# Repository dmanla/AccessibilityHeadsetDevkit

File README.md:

# AccessibilityHeadsetDevkit
A development kit for the creation of an accessibility driven platform.

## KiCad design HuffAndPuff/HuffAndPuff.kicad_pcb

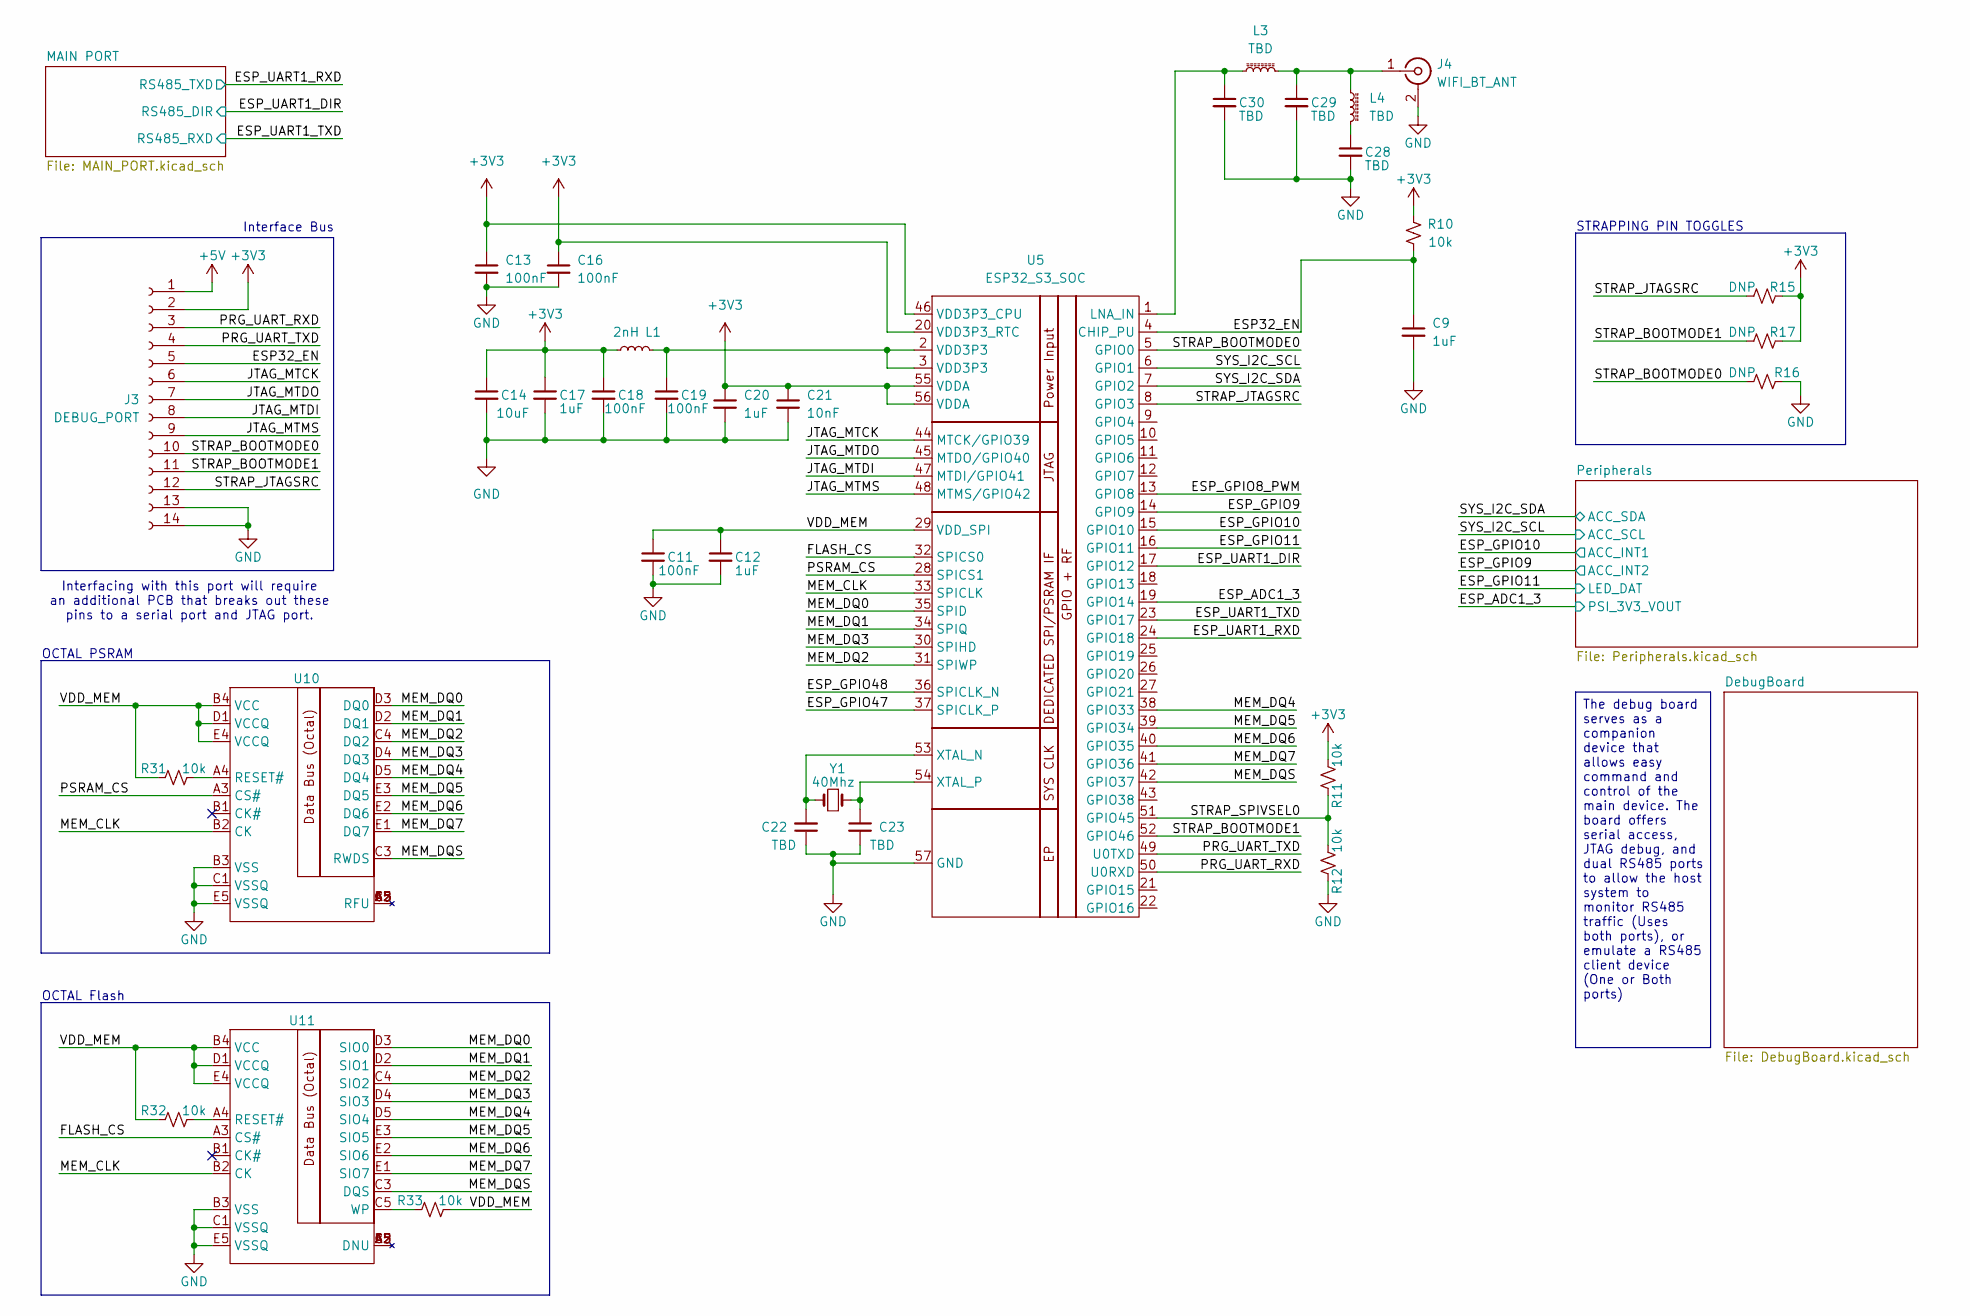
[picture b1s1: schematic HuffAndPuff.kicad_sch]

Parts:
C9, C12, C17, C20: 1uF; C_0402_1005Metric_Pad0.74x0.62mm_HandSolder
C11, C13, C16, C18, C19: 100nF; C_0402_1005Metric_Pad0.74x0.62mm_HandSolder
C14: 10uF; C_0603_1608Metric_Pad1.08x0.95mm_HandSolder
C21: 10nF; C_0402_1005Metric_Pad0.74x0.62mm_HandSolder
C22, C23, C28, C29, C30: TBD; C_0402_1005Metric_Pad0.74x0.62mm_HandSolder
J3: DEBUG_PORT; TE_1-1734839-4_1x14-1MP_P0.5mm_Horizontal
J4: WIFI_BT_ANT; SMA_Molex_73251-2200_Horizontal
L1: 2nH; L_0402_1005Metric_Pad0.77x0.64mm_HandSolder
L3, L4: TBD; L_0402_1005Metric_Pad0.77x0.64mm_HandSolder
R10, R11, R12, R31, R32, R33: 10k; R_0402_1005Metric_Pad0.72x0.64mm_HandSolder
R15, R16, R17: DNP; R_0805_2012Metric_Pad1.20x1.40mm_HandSolder
U5: ESP32_S3_SOC; QFN-56-1EP_7x7mm_P0.4mm_EP5.6x5.6mm
U10, U11: BGA-24_5x5_6.0x8.0mm
Y1: 40Mhz; Crystal_SMD_3215-2Pin_3.2x1.5mm

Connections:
+3V3: C13.1, C14.1, C16.1, C17.1, C18.1, C20.1, C21.1, J3.2, L1.1, R10.1, R11.1, R15.2, R17.2, U5.20 (VDD3P3_RTC), U5.46 (VDD3P3_CPU), U5.55 (VDDA), U5.56 (VDDA); also elsewhere on the board
+5V: J3.1; also elsewhere on the board
/ESP32_EN: C9.1, J3.5, R10.2, U5.4 (CHIP_PU)
/ESP_ADC1_3: U5.19 (GPIO14); also elsewhere on the board
/ESP_GPIO8_PWM: U5.13 (GPIO8)
/ESP_GPIO9: U5.14 (GPIO9); also elsewhere on the board
/ESP_GPIO10: U5.15 (GPIO10); also elsewhere on the board
/ESP_GPIO11: U5.16 (GPIO11); also elsewhere on the board
/ESP_GPIO47: U5.37 (SPICLK_P)
/ESP_GPIO48: U5.36 (SPICLK_N)
/ESP_UART1_DIR: U5.17 (GPIO12); also elsewhere on the board
/ESP_UART1_RXD: U5.24 (GPIO18); also elsewhere on the board
/ESP_UART1_TXD: U5.23 (GPIO17); also elsewhere on the board
/FLASH_CS: U5.32 (SPICS0), U11.A3 (CS#)
/JTAG_MTCK: J3.6, U5.44 (MTCK/GPIO39)
/JTAG_MTDI: J3.8, U5.47 (MTDI/GPIO41)
/JTAG_MTDO: J3.7, U5.45 (MTDO/GPIO40)
/JTAG_MTMS: J3.9, U5.48 (MTMS/GPIO42)
/MEM_CLK: U5.33 (SPICLK), U10.B2 (CK), U11.B2 (CK)
/MEM_DQ0: U5.35 (SPID), U10.D3 (DQ0), U11.D3 (SIO0)
/MEM_DQ1: U5.34 (SPIQ), U10.D2 (DQ1), U11.D2 (SIO1)
/MEM_DQ2: U5.31 (SPIWP), U10.C4 (DQ2), U11.C4 (SIO2)
/MEM_DQ3: U5.30 (SPIHD), U10.D4 (DQ3), U11.D4 (SIO3)
/MEM_DQ4: U5.38 (GPIO33), U10.D5 (DQ4), U11.D5 (SIO4)
/MEM_DQ5: U5.39 (GPIO34), U10.E3 (DQ5), U11.E3 (SIO5)
/MEM_DQ6: U5.40 (GPIO35), U10.E2 (DQ6), U11.E2 (SIO6)
/MEM_DQ7: U5.41 (GPIO36), U10.E1 (DQ7), U11.E1 (SIO7)
/MEM_DQS: U5.42 (GPIO37), U10.C3 (RWDS), U11.C3 (DQS)
/PRG_UART_RXD: J3.3, U5.50 (U0RXD)
/PRG_UART_TXD: J3.4, U5.49 (U0TXD)
/PSRAM_CS: U5.28 (SPICS1), U10.A3 (CS#)
/STRAP_BOOTMODE0: J3.10, R16.1, U5.5 (GPIO0)
/STRAP_BOOTMODE1: J3.11, R17.1, U5.52 (GPIO46)
/STRAP_JTAGSRC: J3.12, R15.1, U5.8 (GPIO3)
/STRAP_SPIVSEL0: R11.2, R12.1, U5.51 (GPIO45)
/SYS_I2C_SCL: U5.6 (GPIO1); also elsewhere on the board
/SYS_I2C_SDA: U5.7 (GPIO2); also elsewhere on the board
/VDD_MEM: C11.1, C12.1, R31.1, R32.1, R33.2, U5.29 (VDD_SPI), U10.B4 (VCC), U10.D1 (VCCQ), U10.E4 (VCCQ), U11.B4 (VCC), U11.D1 (VCCQ), U11.E4 (VCCQ)
GND: C9.2, C11.2, C12.2, C13.2, C14.2, C16.2, C17.2, C18.2, C19.2, C20.2, C21.2, C22.1, C23.2, C28.2, C29.2, C30.2, J3.13, J3.14, J4.2 (Ext), R12.2, R16.2, U5.57 (GND), U10.B3 (VSS), U10.C1 (VSSQ), U10.E5 (VSSQ), U11.B3 (VSS), U11.C1 (VSSQ), U11.E5 (VSSQ); also elsewhere on the board
unnamed: C19.1, L1.2, U5.2 (VDD3P3), U5.3 (VDD3P3)
unnamed: C28.1, L4.2
unnamed: C29.1, J4.1 (In), L3.2, L4.1
unnamed: C30.1, L3.1, U5.1 (LNA_IN)
unnamed: C22.2, U5.53 (XTAL_N), Y1.2
unnamed: C23.1, U5.54 (XTAL_P), Y1.1
unnamed: R31.2, U10.A4 (RESET#)
unnamed: R32.2, U11.A4 (RESET#)
unnamed: R33.1, U11.C5 (WP)

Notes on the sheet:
Interfacing with this port will require an additional PCB that breaks out these pins to a serial port and JTAG port.
STRAPPING PIN TOGGLES
Interface Bus
OCTAL Flash
OCTAL PSRAM
The debug board serves as a companion device that allows easy command and control of the main device. The board offers serial access, JTAG debug, and dual RS485 ports to allow the host system to monitor RS485 traffic (Uses both ports), or emulate a RS485 client device (One or Both ports)

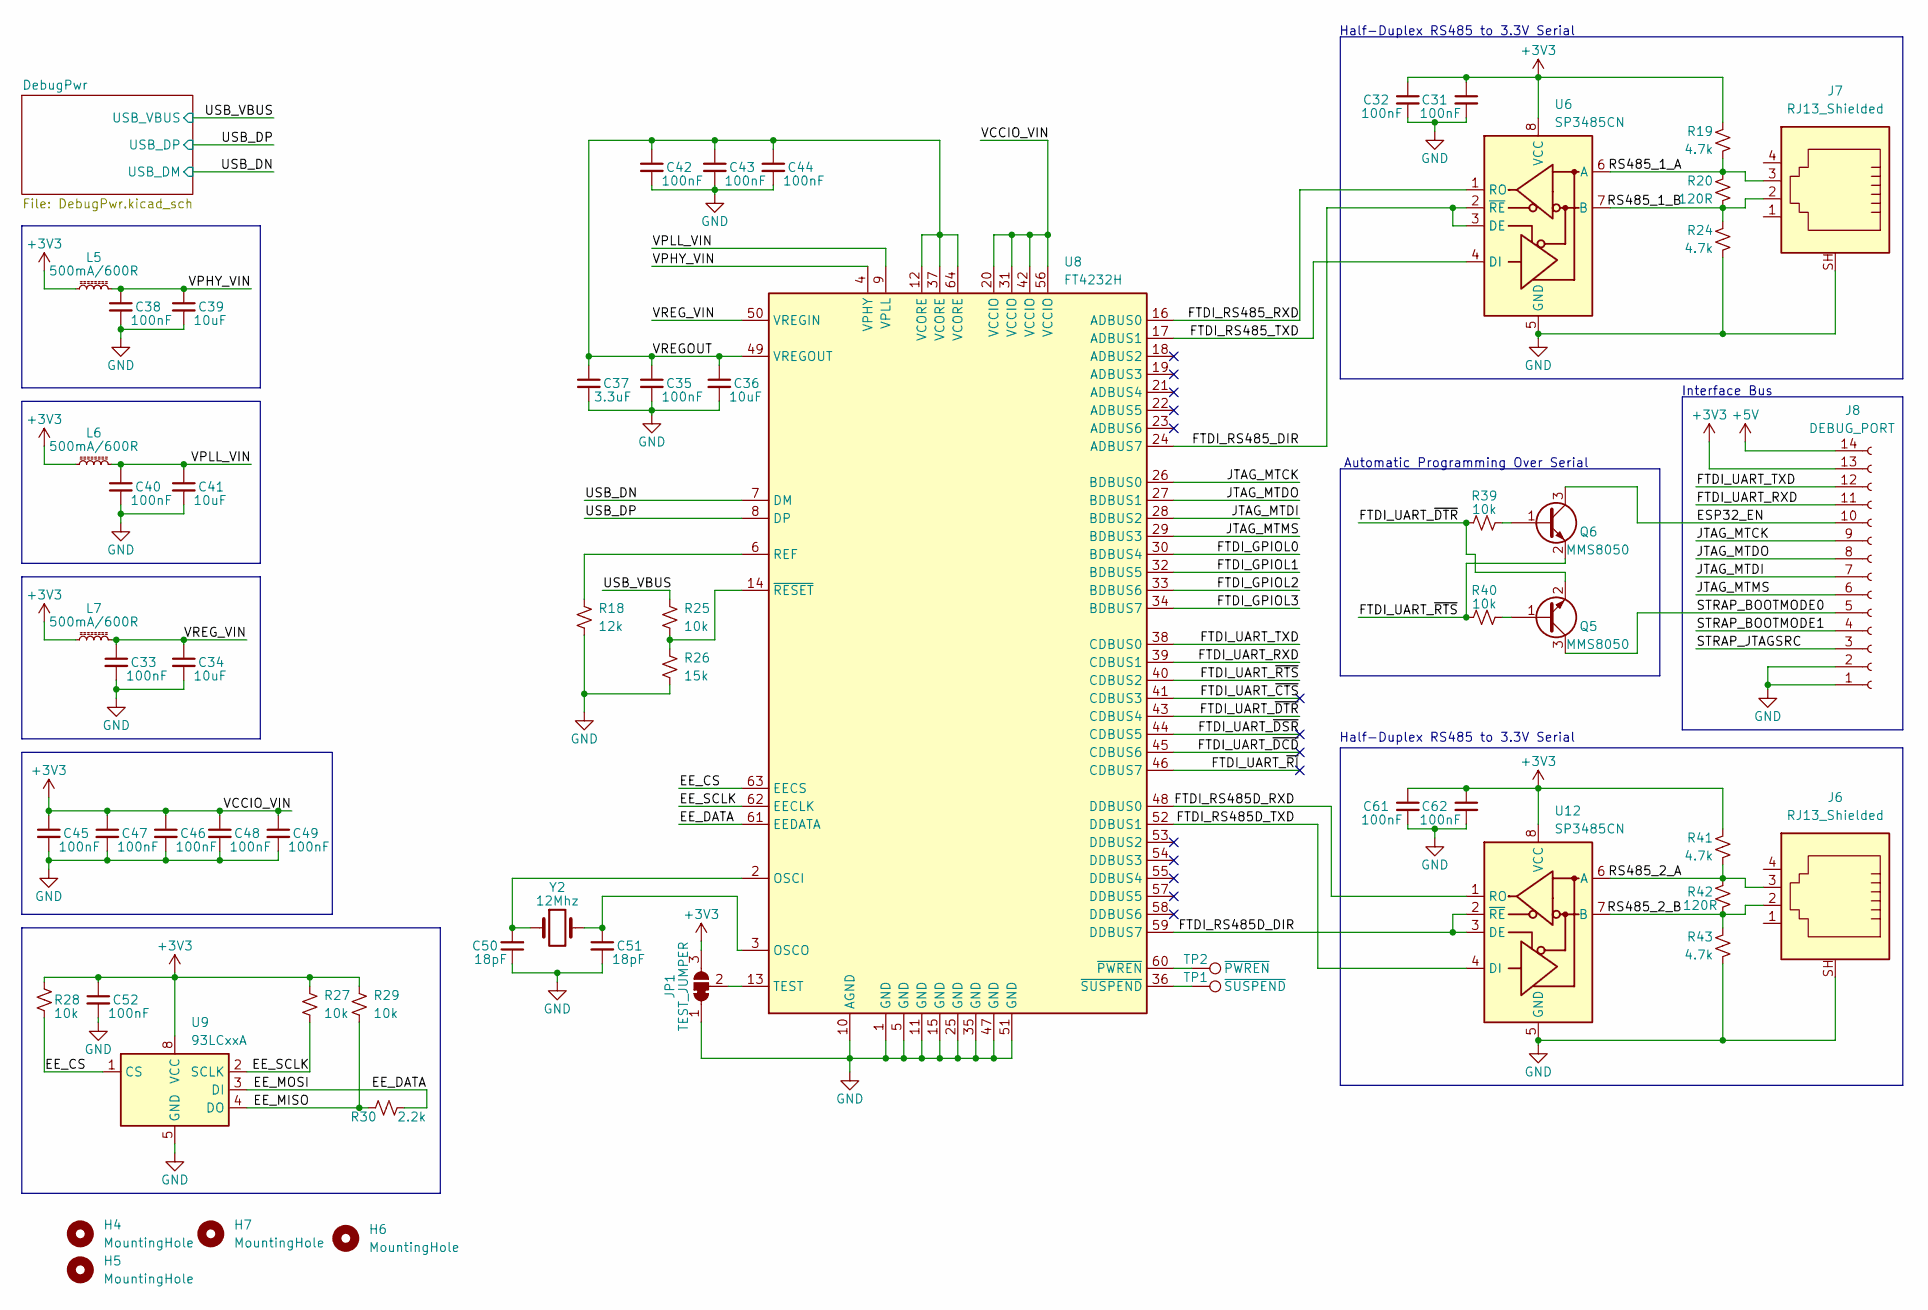
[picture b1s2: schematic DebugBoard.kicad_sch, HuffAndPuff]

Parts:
C31, C32, C33, C35, C38, C40, C42, C43, C44, C45, C46, C47, C48, C49, C52, C61, C62: 100nF; C_0402_1005Metric_Pad0.74x0.62mm_HandSolder
C34, C36, C39, C41: 10uF; C_0603_1608Metric_Pad1.08x0.95mm_HandSolder
C37: 3.3uF; C_0603_1608Metric_Pad1.08x0.95mm_HandSolder
C50, C51: 18pF; C_0402_1005Metric_Pad0.74x0.62mm_HandSolder
H4, H5, H6, H7: MountingHole; MountingHole_2.2mm_M2_ISO7380
J6, J7: RJ13_Shielded; RJ14_Connfly_DS1133-S4_Horizontal
J8: DEBUG_PORT; TE_1-1734839-4_1x14-1MP_P0.5mm_Horizontal
JP1: TEST_JUMPER; SolderJumper-3_P1.3mm_Bridged12_RoundedPad1.0x1.5mm
L5, L6, L7: 500mA/600R; L_0603_1608Metric_Pad1.05x0.95mm_HandSolder
Q5, Q6: MMS8050; SOT-23-3
R18: 12k; L_0402_1005Metric_Pad0.77x0.64mm_HandSolder
R19, R24, R41, R43: 4.7k; R_0402_1005Metric_Pad0.72x0.64mm_HandSolder
R20, R42: 120R; R_0805_2012Metric_Pad1.20x1.40mm_HandSolder
R25, R27, R28, R29, R39, R40: 10k; L_0402_1005Metric_Pad0.77x0.64mm_HandSolder
R26: 15k; L_0402_1005Metric_Pad0.77x0.64mm_HandSolder
R30: 2.2k; L_0402_1005Metric_Pad0.77x0.64mm_HandSolder
TP1: ~{SUSPEND}; TestPoint_Pad_1.5x1.5mm
TP2: ~{PWREN}; TestPoint_Pad_1.5x1.5mm
U6, U12: SP3485CN; SOIC-8_3.9x4.9mm_P1.27mm
U8: FT4232H; QFN-64-1EP_8x8mm_P0.4mm_EP6.5x6.5mm
U9: 93LCxxA; DFN-8_2x2mm_P0.5mm
Y2: 12Mhz; Crystal_SMD_3215-2Pin_3.2x1.5mm

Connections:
+3V3: C31.1, C32.1, C45.1, C46.1, C47.1, C48.1, C49.1, C52.1, C61.1, C62.1, J8.13, JP1.3 (B), L5.1, L6.1, L7.1, R19.2, R27.1, R28.1, R29.1, R41.2, U6.8 (VCC), U8.20 (VCCIO), U8.31 (VCCIO), U8.42 (VCCIO), U8.56 (VCCIO), U9.8 (VCC), U12.8 (VCC); also elsewhere on the board
+5V: J8.14; also elsewhere on the board
/DebugBoard/EE_CS: R28.2, U8.63 (EECS), U9.1 (CS)
/DebugBoard/EE_DATA: R30.2, U8.61 (EEDATA), U9.3 (DI)
/DebugBoard/EE_MISO: R29.2, R30.1, U9.4 (DO)
/DebugBoard/EE_SCLK: R27.2, U8.62 (EECLK), U9.2 (SCLK)
/DebugBoard/ESP32_EN: J8.10, Q6.3 (C)
/DebugBoard/FTDI_GPIOL0: U8.30 (BDBUS4)
/DebugBoard/FTDI_GPIOL1: U8.32 (BDBUS5)
/DebugBoard/FTDI_GPIOL2: U8.33 (BDBUS6)
/DebugBoard/FTDI_GPIOL3: U8.34 (BDBUS7)
/DebugBoard/FTDI_RS485D_DIR: U8.59 (DDBUS7), U12.2 (~RE), U12.3 (DE)
/DebugBoard/FTDI_RS485D_RXD: U8.48 (DDBUS0), U12.1 (RO)
/DebugBoard/FTDI_RS485D_TXD: U8.52 (DDBUS1), U12.4 (DI)
/DebugBoard/FTDI_RS485_DIR: U6.2 (~RE), U6.3 (DE), U8.24 (ADBUS7)
/DebugBoard/FTDI_RS485_RXD: U6.1 (RO), U8.16 (ADBUS0)
/DebugBoard/FTDI_RS485_TXD: U6.4 (DI), U8.17 (ADBUS1)
/DebugBoard/FTDI_UART_RXD: J8.11, U8.39 (CDBUS1)
/DebugBoard/FTDI_UART_TXD: J8.12, U8.38 (CDBUS0)
/DebugBoard/FTDI_UART_~CTS: U8.41 (CDBUS3)
/DebugBoard/FTDI_UART_~DCD: U8.45 (CDBUS6)
/DebugBoard/FTDI_UART_~DSR: U8.44 (CDBUS5)
/DebugBoard/FTDI_UART_~DTR: Q5.2 (E), R39.1, U8.43 (CDBUS4)
/DebugBoard/FTDI_UART_~RI: U8.46 (CDBUS7)
/DebugBoard/FTDI_UART_~RTS: Q6.2 (E), R40.1, U8.40 (CDBUS2)
/DebugBoard/JTAG_MTCK: J8.9, U8.26 (BDBUS0)
/DebugBoard/JTAG_MTDI: J8.7, U8.28 (BDBUS2)
/DebugBoard/JTAG_MTDO: J8.8, U8.27 (BDBUS1)
/DebugBoard/JTAG_MTMS: J8.6, U8.29 (BDBUS3)
/DebugBoard/RS485_1_A: J7.3, R19.1, R20.2, U6.6 (A)
/DebugBoard/RS485_1_B: J7.2, R20.1, R24.2, U6.7 (B)
/DebugBoard/RS485_2_A: J6.3, R41.1, R42.2, U12.6 (A)
/DebugBoard/RS485_2_B: J6.2, R42.1, R43.2, U12.7 (B)
/DebugBoard/STRAP_BOOTMODE0: J8.5, Q5.3 (C)
/DebugBoard/STRAP_BOOTMODE1: J8.4
/DebugBoard/STRAP_JTAGSRC: J8.3
/DebugBoard/USB_DN: U8.7 (DM); also elsewhere on the board
/DebugBoard/USB_DP: U8.8 (DP); also elsewhere on the board
/DebugBoard/USB_VBUS: R25.1; also elsewhere on the board
/DebugBoard/VPHY_VIN: C38.1, C39.1, L5.2, U8.4 (VPHY)
/DebugBoard/VPLL_VIN: C40.1, C41.1, L6.2, U8.9 (VPLL)
/DebugBoard/VREGOUT: C35.1, C36.1, C37.1, C42.1, C43.1, C44.1, U8.12 (VCORE), U8.37 (VCORE), U8.49 (VREGOUT), U8.64 (VCORE)
/DebugBoard/VREG_VIN: C33.1, C34.1, L7.2, U8.50 (VREGIN)
GND: C31.2, C32.2, C33.2, C34.2, C35.2, C36.2, C37.2, C38.2, C39.2, C40.2, C41.2, C42.2, C43.2, C44.2, C45.2, C46.2, C47.2, C48.2, C49.2, C50.1, C51.2, C52.2, C61.2, C62.2, J6.SH, J7.SH, J8.1, J8.2, JP1.1 (A), R18.2, R24.1, R26.2, R43.1, U6.5 (GND), U8.1 (GND), U8.5 (GND), U8.10 (AGND), U8.11 (GND), U8.15 (GND), U8.25 (GND), U8.35 (GND), U8.47 (GND), U8.51 (GND), U9.5 (GND), U12.5 (GND); also elsewhere on the board
unnamed: JP1.2 (C), U8.13 (TEST)
unnamed: Q5.1 (B), R40.2
unnamed: Q6.1 (B), R39.2
unnamed: C50.2, U8.2 (OSCI), Y2.1
unnamed: C51.1, U8.3 (OSCO), Y2.2
unnamed: R18.1, U8.6 (REF)
unnamed: TP2.1, U8.60 (~PWREN)
unnamed: R25.2, R26.1, U8.14 (~RESET)
unnamed: TP1.1, U8.36 (~SUSPEND)

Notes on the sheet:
Interface Bus
Half-Duplex RS485 to 3.3V Serial
Automatic Programming Over Serial

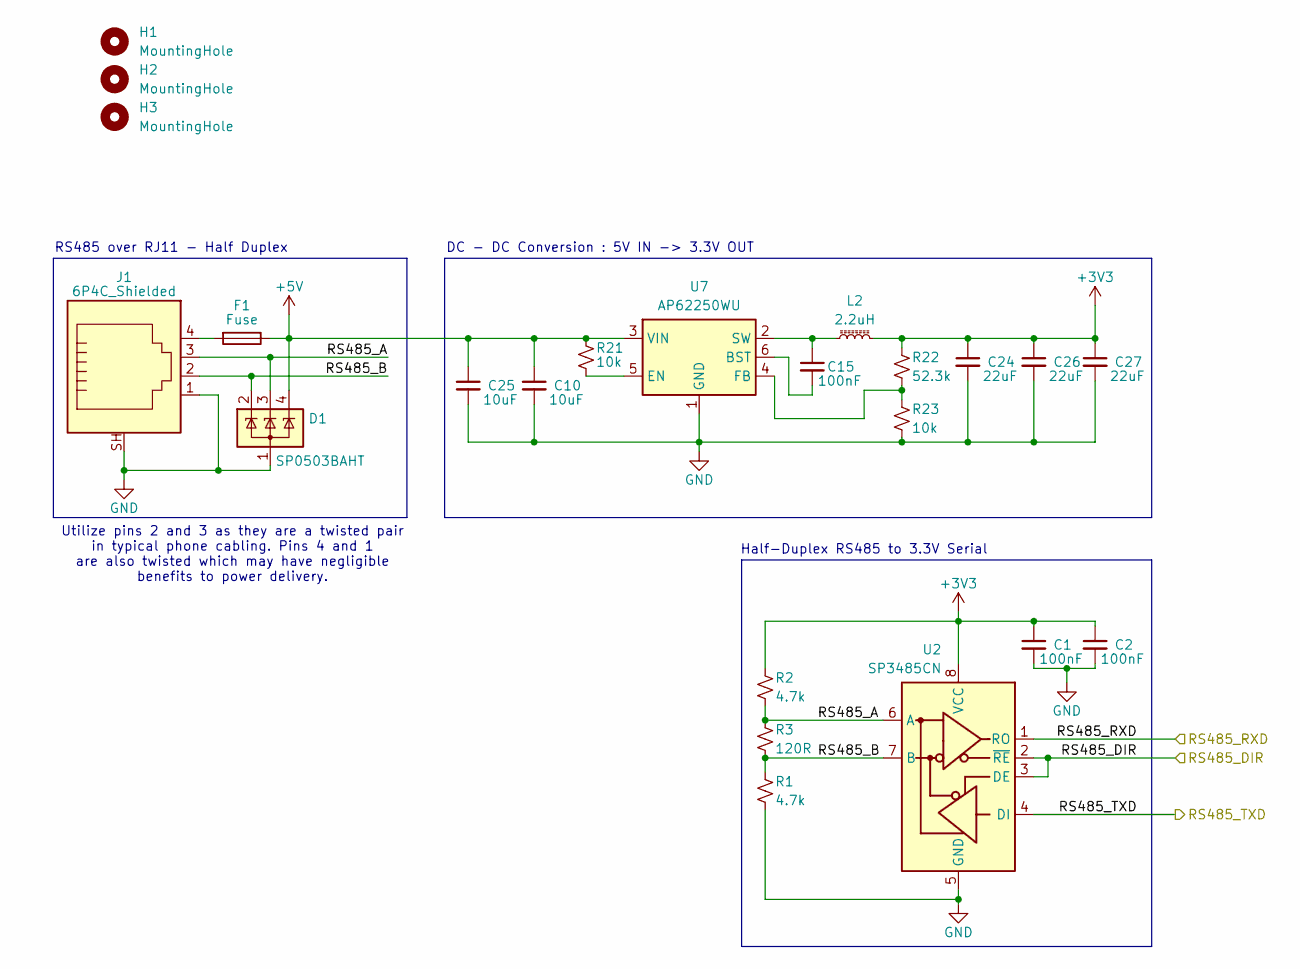
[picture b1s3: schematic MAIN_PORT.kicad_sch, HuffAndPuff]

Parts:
C1, C2, C15: 100nF; C_0402_1005Metric_Pad0.74x0.62mm_HandSolder
C10, C25: 10uF; C_0402_1005Metric_Pad0.74x0.62mm_HandSolder
C24, C26, C27: 22uF; C_0805_2012Metric_Pad1.18x1.45mm_HandSolder
D1: SP0503BAHT; SOT-143
F1: Fuse; Fuse_0603_1608Metric_Pad1.05x0.95mm_HandSolder
H1, H2, H3: MountingHole; MountingHole_2.2mm_M2_ISO7380
J1: 6P4C_Shielded; RJ14_Connfly_DS1133-S4_Horizontal
L2: 2.2uH; L_1210_3225Metric_Pad1.42x2.65mm_HandSolder
R1, R2: 4.7k; R_0402_1005Metric_Pad0.72x0.64mm_HandSolder
R3: 120R; R_0805_2012Metric_Pad1.20x1.40mm_HandSolder
R21, R23: 10k; R_0402_1005Metric_Pad0.72x0.64mm_HandSolder
R22: 52.3k; R_0402_1005Metric_Pad0.72x0.64mm_HandSolder
U2: SP3485CN; SOIC-8_3.9x4.9mm_P1.27mm
U7: AP62250WU; TSOT-23-6

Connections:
+3V3: C1.1, C2.1, C24.1, C26.1, C27.1, L2.2, R2.2, R22.2, U2.8 (VCC); also elsewhere on the board
+5V: C10.1, C25.1, D1.4 (K), F1.1, R21.1, U7.3 (VIN); also elsewhere on the board
/ESP_UART1_DIR: U2.2 (~RE), U2.3 (DE); also elsewhere on the board
/ESP_UART1_RXD: U2.4 (DI); also elsewhere on the board
/ESP_UART1_TXD: U2.1 (RO); also elsewhere on the board
/MAIN PORT/RS485_A: D1.3 (K), J1.3, R2.1, R3.2, U2.6 (A)
/MAIN PORT/RS485_B: D1.2 (K), J1.2, R1.2, R3.1, U2.7 (B)
GND: C1.2, C2.2, C10.2, C24.2, C25.2, C26.2, C27.2, D1.1 (A), J1.1, J1.SH, R1.1, R23.1, U2.5 (GND), U7.1 (GND); also elsewhere on the board
unnamed: F1.2, J1.4
unnamed: C15.2, U7.6 (BST)
unnamed: R21.2, U7.5 (EN)
unnamed: R22.1, R23.2, U7.4 (FB)
unnamed: C15.1, L2.1, U7.2 (SW)

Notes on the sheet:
Half-Duplex RS485 to 3.3V Serial
DC - DC Conversion : 5V IN -> 3.3V OUT
RS485 over RJ11 - Half Duplex
Utilize pins 2 and 3 as they are a twisted pair in typical phone cabling. Pins 4 and 1 are also twisted which may have negligible benefits to power delivery.

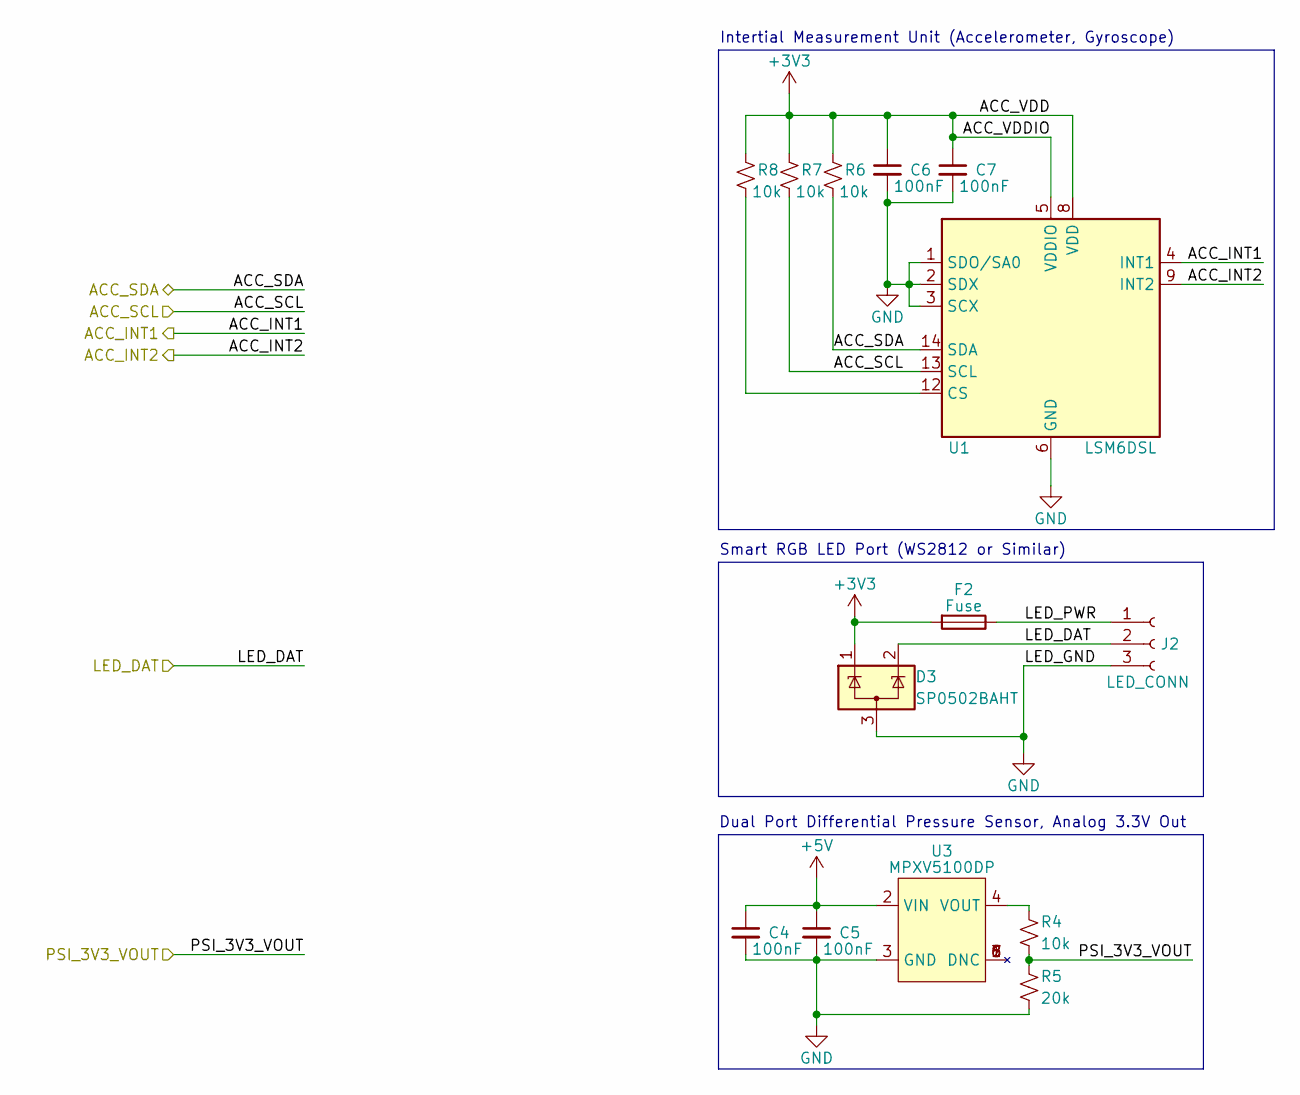
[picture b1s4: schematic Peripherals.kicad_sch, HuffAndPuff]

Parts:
C4, C5, C6, C7: 100nF; C_0402_1005Metric_Pad0.74x0.62mm_HandSolder
D3: SP0502BAHT; SOT-23
F2: Fuse; Fuse_0603_1608Metric_Pad1.05x0.95mm_HandSolder
J2: LED_CONN; JST_PH_S3B-PH-K_1x03_P2.00mm_Horizontal
R4, R6, R7, R8: 10k; R_0402_1005Metric_Pad0.72x0.64mm_HandSolder
R5: 20k; R_0402_1005Metric_Pad0.72x0.64mm_HandSolder
U1: LSM6DSL; LGA-14_3x2.5mm_P0.5mm_LayoutBorder3x4y
U3: MPXV5100DP; BSOP-8-W16.76-H7.62-P2.54

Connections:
+3V3: C6.1, C7.1, D3.1 (K), F2.2, R6.1, R7.1, R8.1, U1.5 (VDDIO), U1.8 (VDD); also elsewhere on the board
+5V: C4.1, C5.1, U3.2 (VIN); also elsewhere on the board
/ESP_ADC1_3: R4.2, R5.1; also elsewhere on the board
/ESP_GPIO9: U1.9 (INT2); also elsewhere on the board
/ESP_GPIO10: U1.4 (INT1); also elsewhere on the board
/ESP_GPIO11: D3.2 (K), J2.2; also elsewhere on the board
/Peripherals/LED_PWR: F2.1, J2.1
/SYS_I2C_SCL: R7.2, U1.13 (SCL); also elsewhere on the board
/SYS_I2C_SDA: R6.2, U1.14 (SDA); also elsewhere on the board
GND: C4.2, C5.2, C6.2, C7.2, D3.3 (A), J2.3, R5.2, U1.1 (SDO/SA0), U1.2 (SDX), U1.3 (SCX), U1.6 (GND), U1.7 (GND), U3.3 (GND); also elsewhere on the board
unnamed: R8.2, U1.12 (CS)
unnamed: R4.1, U3.4 (VOUT)

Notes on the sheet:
Smart RGB LED Port (WS2812 or Similar)
Dual Port Differential Pressure Sensor, Analog 3.3V Out
Intertial Measurement Unit (Accelerometer, Gyroscope)

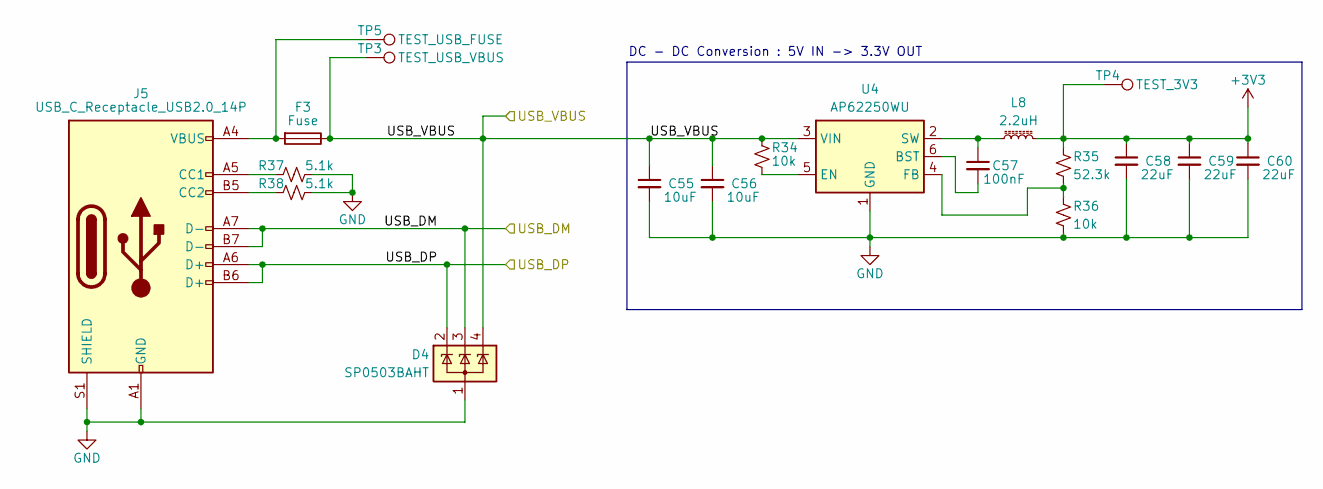
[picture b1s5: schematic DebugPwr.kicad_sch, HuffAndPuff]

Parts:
C55, C56: 10uF; C_0603_1608Metric_Pad1.08x0.95mm_HandSolder
C57: 100nF; C_0402_1005Metric_Pad0.74x0.62mm_HandSolder
C58, C59, C60: 22uF; C_0805_2012Metric_Pad1.18x1.45mm_HandSolder
D4: SP0503BAHT; SOT-143
F3: Fuse; Fuse_0603_1608Metric_Pad1.05x0.95mm_HandSolder
J5: USB_C_Receptacle_USB2.0_14P; USB_C_Receptacle_G-Switch_GT-USB-7010ASV
L8: 2.2uH; L_1210_3225Metric_Pad1.42x2.65mm_HandSolder
R34, R36: 10k; R_0402_1005Metric_Pad0.72x0.64mm_HandSolder
R35: 52.3k; R_0402_1005Metric_Pad0.72x0.64mm_HandSolder
R37, R38: 5.1k; R_0402_1005Metric_Pad0.72x0.64mm_HandSolder
TP3: TEST_USB_VBUS; TestPoint_Pad_1.5x1.5mm
TP4: TEST_3V3; TestPoint_Pad_1.5x1.5mm
TP5: TEST_USB_FUSE; TestPoint_Pad_1.5x1.5mm
U4: AP62250WU; TSOT-23-6

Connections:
+3V3: C58.1, C59.1, C60.1, L8.2, R35.2, TP4.1; also elsewhere on the board
/DebugBoard/USB_DN: D4.3 (K), J5.A7 (D-), J5.B7 (D-); also elsewhere on the board
/DebugBoard/USB_DP: D4.2 (K), J5.A6 (D+), J5.B6 (D+); also elsewhere on the board
/DebugBoard/USB_VBUS: C55.1, C56.1, D4.4 (K), F3.1, R34.1, TP3.1, U4.3 (VIN); also elsewhere on the board
GND: C55.2, C56.2, C58.2, C59.2, C60.2, D4.1 (A), J5.A1 (GND), J5.A12 (GND), J5.B1 (GND), J5.B12 (GND), J5.S1 (SHIELD), R36.1, R37.2, R38.2, U4.1 (GND); also elsewhere on the board
unnamed: F3.2, J5.A4 (VBUS), J5.A9 (VBUS), J5.B4 (VBUS), J5.B9 (VBUS), TP5.1
unnamed: J5.A5 (CC1), R37.1
unnamed: J5.B5 (CC2), R38.1
unnamed: C57.2, U4.6 (BST)
unnamed: R34.2, U4.5 (EN)
unnamed: R35.1, R36.2, U4.4 (FB)
unnamed: C57.1, L8.1, U4.2 (SW)

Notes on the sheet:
DC - DC Conversion : 5V IN -> 3.3V OUT

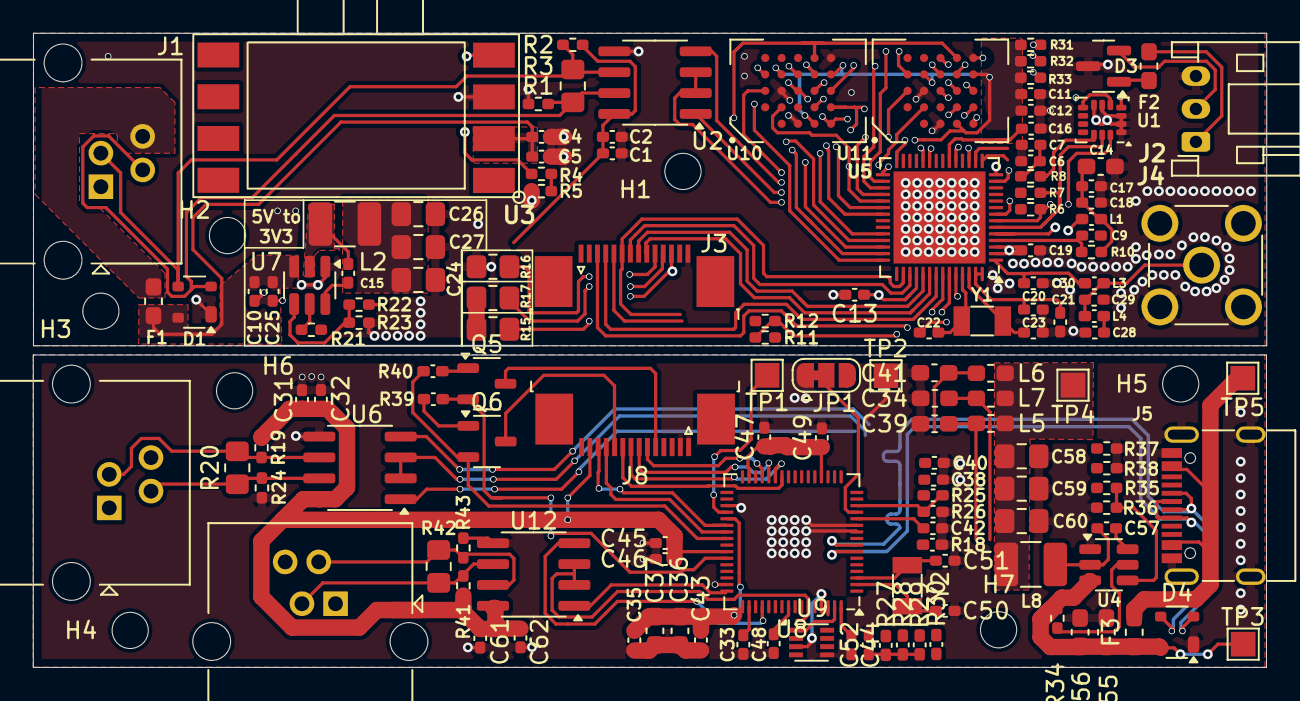
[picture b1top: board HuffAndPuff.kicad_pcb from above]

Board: 4 copper layers, 75.0 x 38.6 mm, 149 parts (0 on the bottom side), 102 nets.

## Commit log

2025-05-17 license
2025-05-17 schematic for users without kicad
